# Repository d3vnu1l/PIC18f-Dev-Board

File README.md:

# PIC18f-Dev-Board
Development board for PIC18f. Pins are broken out to female pin headers, routed along the edges of the board and reorganized logically. Includes full speed USB connectivity, high speed external oscillator, and status LED's.

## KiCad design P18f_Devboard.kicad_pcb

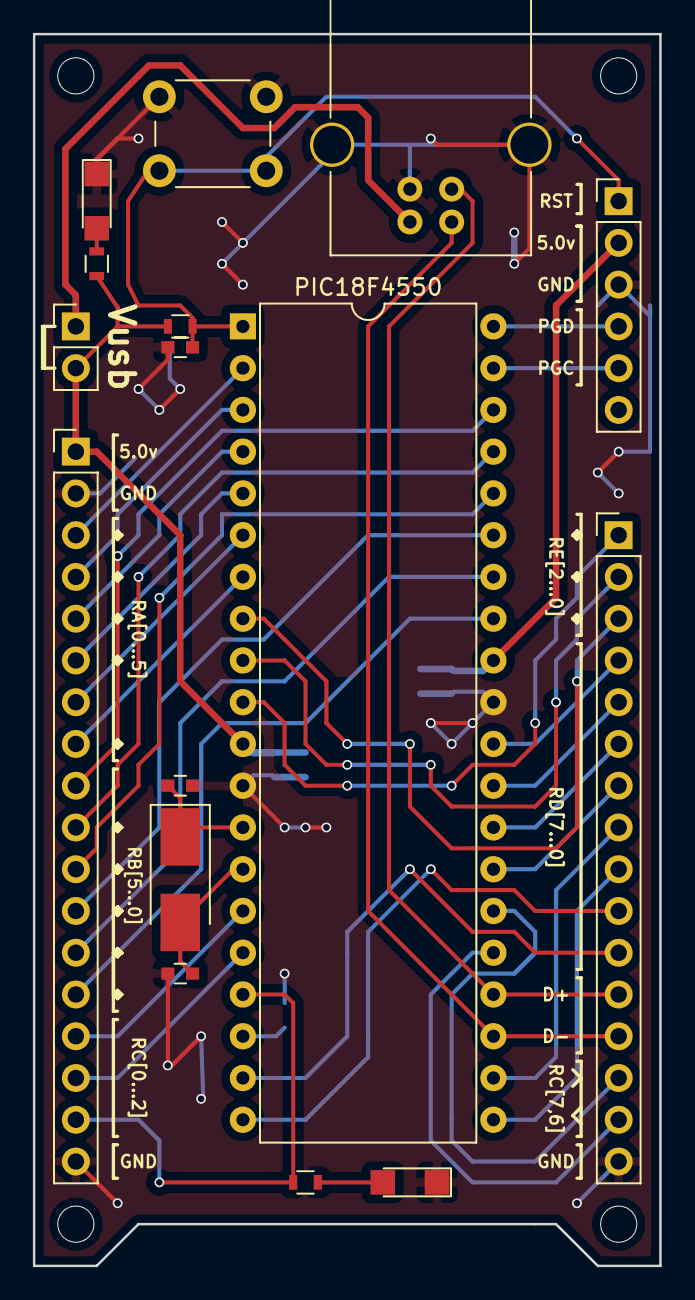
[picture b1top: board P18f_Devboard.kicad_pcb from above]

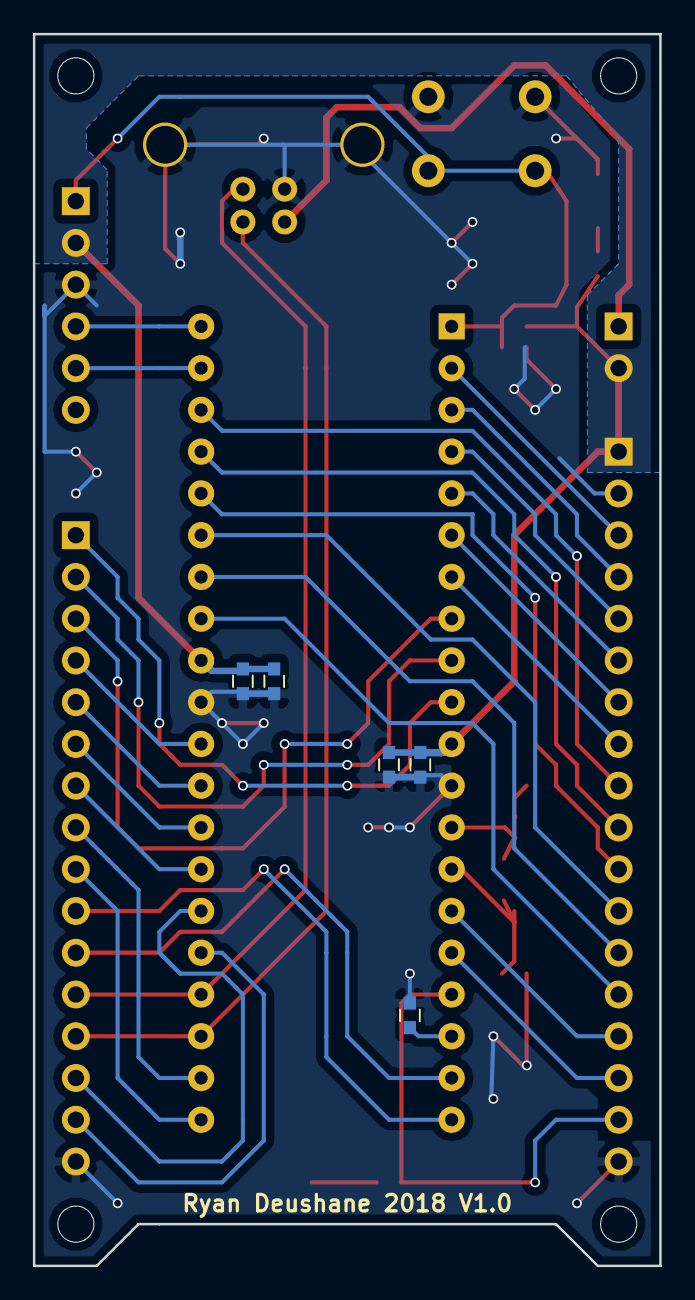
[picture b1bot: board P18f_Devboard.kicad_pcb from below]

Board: 2 copper layers, 38.1 x 74.9 mm, 21 parts (5 on the bottom side), 41 nets.

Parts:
C1, C2, C7, C8: 1.0u; C_0603
C5, C6: 100N; C_0603
C9, C11: 22p; C_0603
D2, D3: LED; LED_1206
J1: Conn_01x18_Female; Socket_Strip_Straight_1x18_Pitch2.54mm
J2: Conn_01x02_Male; Pin_Header_Straight_1x02_Pitch2.54mm
J3: USB_B
J4: Conn_01x06_Male; Pin_Header_Straight_1x06_Pitch2.54mm
J5: Conn_01x16_Female; Socket_Strip_Straight_1x16_Pitch2.54mm
PIC18F4550: PIC18LF4550-I/P; DIP-40_W15.24mm
R2, R3: 270; R_0603
R4: 10K; R_0603
SW1: SW_DIP_x01; SW_PUSH_6mm
Y1: 20Mhz; Crystal_SMD_5032-2pin_5.0x3.2mm_HandSoldering

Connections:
+5V: C5.1, C6.2, C7.1, C8.2, J1.1, J2.2, J4.2, PIC18F4550.11, PIC18F4550.32, R3.1, R4.2
/D+: J3.3, J5.12, PIC18F4550.24
/D-: J3.2, J5.13, PIC18F4550.23
/PA0: J1.3, PIC18F4550.2
/PA1: J1.4, PIC18F4550.3
/PA2: J1.5, PIC18F4550.4
/PA3: J1.6, PIC18F4550.5
/PA4: J1.7, PIC18F4550.6
/PA5: J1.8, PIC18F4550.7
/PB0: J1.14, PIC18F4550.33
/PB1: J1.13, PIC18F4550.34
/PB2: J1.12, PIC18F4550.35
/PB3: J1.11, PIC18F4550.36
/PB4: J1.10, PIC18F4550.37
/PB5: J1.9, PIC18F4550.38
/PGC: J4.5, PIC18F4550.39
/PGD: J4.4, PIC18F4550.40
/RC0: J1.15, PIC18F4550.15
/RC1: J1.16, PIC18F4550.16
/RC2: J1.17, PIC18F4550.17, R2.1
/RC6: J5.15, PIC18F4550.25
/RC7: J5.14, PIC18F4550.26
/RD0: J5.11, PIC18F4550.19
/RD1: J5.10, PIC18F4550.20
/RD2: J5.9, PIC18F4550.21
/RD3: J5.8, PIC18F4550.22
/RD4: J5.7, PIC18F4550.27
/RD5: J5.6, PIC18F4550.28
/RD6: J5.5, PIC18F4550.29
/RD7: J5.4, PIC18F4550.30
/RE0: J5.3, PIC18F4550.8
/RE1: J5.2, PIC18F4550.9
/RE2: J5.1, PIC18F4550.10
/RESET: C2.1, J4.1, PIC18F4550.1, R4.1, SW1.2
GND: C1.1, C2.2, C5.2, C6.1, C7.2, C8.1, C9.2, C11.2, D2.1, D3.1, J1.2, J1.18, J3.4, J3.5, J4.3, J5.16, PIC18F4550.12, PIC18F4550.31, SW1.1
unnamed: C1.2, PIC18F4550.18
unnamed: C9.1, PIC18F4550.13, Y1.1
unnamed: C11.1, PIC18F4550.14, Y1.2
unnamed: D2.2, R3.2
unnamed: D3.2, R2.2
unnamed: J2.1, J3.1

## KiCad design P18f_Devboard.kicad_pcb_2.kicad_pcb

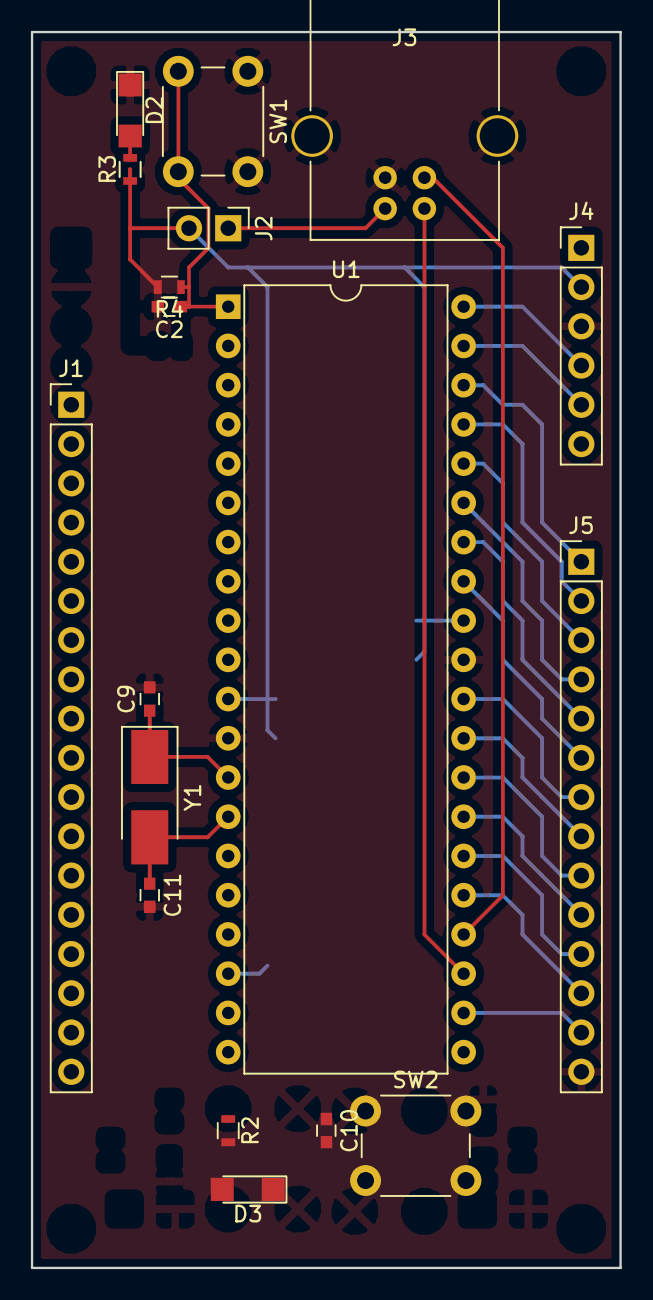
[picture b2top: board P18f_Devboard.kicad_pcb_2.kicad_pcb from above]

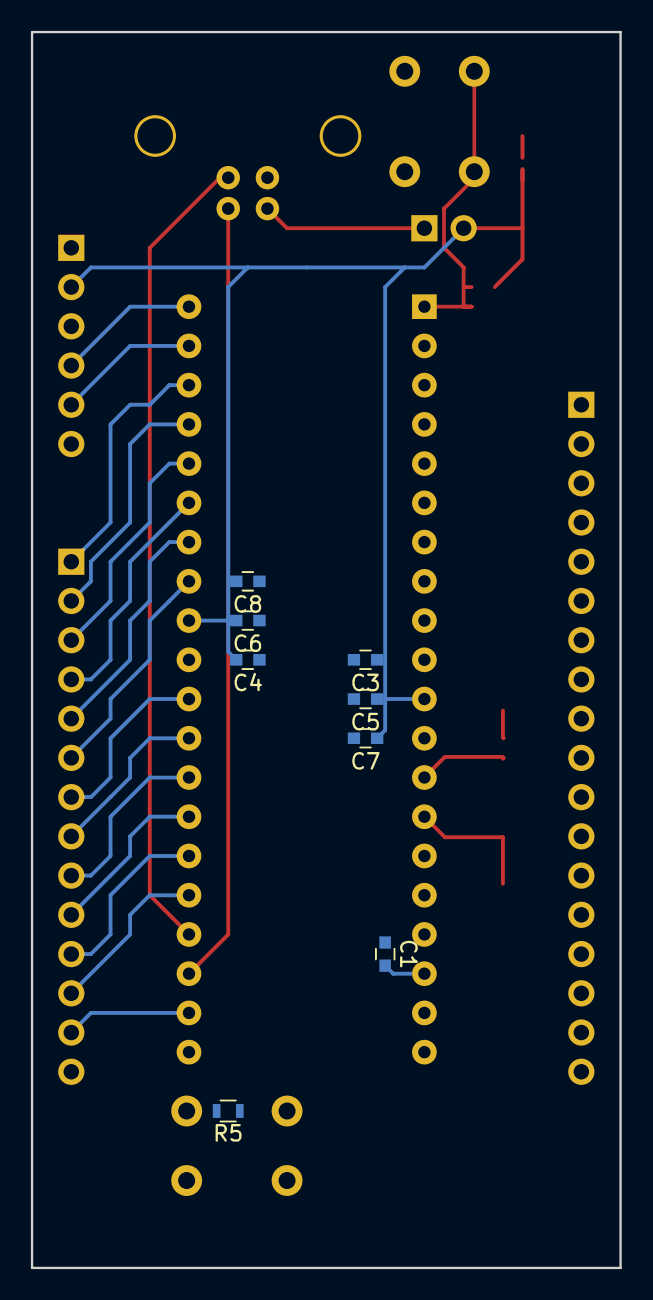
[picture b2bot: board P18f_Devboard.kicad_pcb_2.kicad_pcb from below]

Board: 2 copper layers, 38.1 x 80.0 mm, 26 parts (8 on the bottom side), 14 nets.

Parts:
C1, C2, C7, C8: 1.0u; C_0603
C3, C4, C5, C6: 100N; C_0603
C9, C11: 22p; C_0603
C10: 100n; C_0603
D2, D3: LED; LED_1206
J1: Conn_01x18_Female; Socket_Strip_Straight_1x18_Pitch2.54mm
J2: Conn_01x02_Male; Pin_Header_Straight_1x02_Pitch2.54mm
J3: USB_B
J4: Conn_01x06_Male; Pin_Header_Straight_1x06_Pitch2.54mm
J5: Conn_01x14_Female; Socket_Strip_Straight_1x14_Pitch2.54mm
R2, R3: 270; R_0603
R4, R5: 10K; R_0603
SW1, SW2: SW_DIP_x01; SW_PUSH_6mm
U1: PIC18LF4550-I/P; DIP-40_W15.24mm
Y1: 20Mhz; Crystal_SMD_5032-2pin_5.0x3.2mm_HandSoldering

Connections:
+5V: C3.1, C4.2, C5.1, C6.2, C7.1, C8.2, J1.1, J2.2, J4.2, R3.1, R4.2, R5.2, U1.11, U1.32
/D+: J3.3, J5.12, U1.24
/D-: J3.2, J5.13, U1.23
/PGC: J4.5, U1.39
/PGD: J4.4, U1.40
/RESET: C2.1, J4.1, R4.1, SW1.2, U1.1
GND: C1.1, C2.2, C3.2, C4.1, C5.2, C6.1, C7.2, C8.1, C9.2, C10.2, C11.2, D2.1, D3.1, J1.2, J1.18, J3.4, J3.5, J4.3, J5.14, SW1.1, SW2.2, U1.12, U1.31
unnamed: C1.2, U1.18
unnamed: C9.1, U1.13, Y1.1
unnamed: C10.1, R5.1, SW2.1
unnamed: C11.1, U1.14, Y1.2
unnamed: D2.2, R3.2
unnamed: D3.2, R2.2
unnamed: J2.1, J3.1

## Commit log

2018-04-02 Initial add files
